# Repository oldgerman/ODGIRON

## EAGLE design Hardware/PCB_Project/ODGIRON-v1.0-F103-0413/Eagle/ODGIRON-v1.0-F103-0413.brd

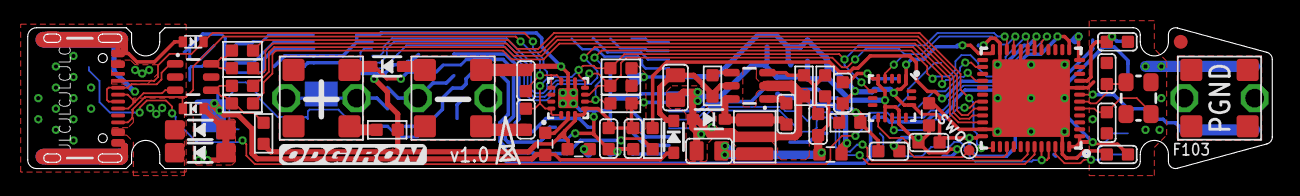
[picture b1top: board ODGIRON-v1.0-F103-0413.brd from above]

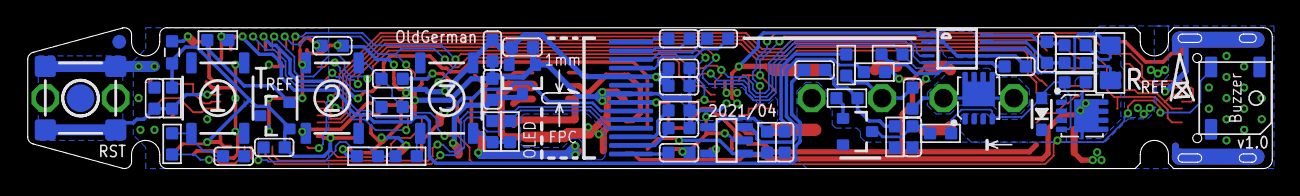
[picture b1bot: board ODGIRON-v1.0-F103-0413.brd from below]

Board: 2 copper layers, 89.8 x 10.2 mm, 123 parts (57 on the bottom side), 66 nets.

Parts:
AMP1: SGM8551XN5G/TR; SOT23-5
BUZ1: BUZZER_5020
C1, C2, C3, C4, C5, C6, C10, C11, C12, C13, C14, C16, C29: 0.1uF/50V; C0603
C7, C23: 4.7uF/10V; C0603
C8, C9: 10pF/50V; C0603
C15, C21, C22, C24, C31, C39: 1uF/16V; C0603
C17, C27: 10nF/50V; C0603
C18, C19: 470pF/50V; C0603
C20, C25, C26, C37: 10uF/10V; C0603
C30: 10uF/25V; C0805
C32: 100pF; C0603
C33: 4.7uF/50V; C0805
C34: 100pF/50V; C0603
CP1: FUSE_CLIPS_01
D1, D7, D9: B5819WS; SOD-323
D2, D5: SMF26A; SOD-123
D3: MMSZ5242BS-7-F; SOD-323
D6, D8: ESD5B5.0ST1; SOD-523
DA1: INA226; MSOP10
FB1, FB2, FB3, FB4, FB5: 1K; F0603
FID1, FID2: FIDUCIAL; FIDUCIAL_1MM
J3: USB-C-16P
L1: 33uH CBC3225T330KR; SMD,3.2X2.5X2.5MM
LCD1: 0.87inch SSD1316; 0.87INCH_128X32_OLED_SSD1306
LOGO1: OSHW-LOGONO_SILK; DUMMY
PAD1, PAD2, PAD3, PAD4, PAD5, PAD6, PAD7, PAD8, PAD9, PAD10, PAD11, PAD12: PADTP16SQ; TP16SQ
Q2, Q3: AON7403; DFN8P-0.65-3X3X0.8MM
Q4: 600mA/40V; SOT23-3
R1, R13: 32.4K; R0603
R2: 124K; R0603
R3, R10, R16, R18, R19, R22, R25, R35: 4.7K; R0603
R4: 1.5K; R0603
R5, R6, R27, R28: 22R; R0603
R7, R12, R23, R41, R45: 1K; R0603
R8, R20, R42: 100K; R0603
R9, R11, R14, R38: 10K; R0603
R17: 560K; R0603
R24: 10mR ±1% ±50ppm/°C; R1206
R36, R37: 10R; R0603
R43: 2.4K ±0.1% ±25ppm/℃; R0603
R44: 750K ±0.1% ±25ppm/℃; R0603
S1, S2, S3, S5: TACTILE_SWITCH_SMD
T1: HAKKO_T12_K-TYPE_WITH_FUSE_CLIPS_X2
TP1: PGND; TESTPOINT_ROUND_2MM
TP5: SWO; PAD.03X.03
U1: FUSB302BMPX; QFN14-2.5X2.5MM
U3: STM32F103CBU6; QFN48_7X7MM_0.5MM
U4: MP2456GJ; SOT23-6
U5: MCP9700AT-E/TT; SOT23-3@1
U6: MCP1700T-3302E/TT; SOT23-3
U8: LIS3DH; LGA-16-3X3
U$3: CREATIVE_COMMONS
VD1: USBLC6-2SC6; SOT23-6
ZO1: 8MHz; 3.2X2.5_KX-7

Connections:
3.9V: C30.1, C32.1, FB1.1, L1.2, R2.1
+3V3: C2.1, C4.1, C5.1, C12.2, C13.2, C14.2, C15.1, C20.2, C23.2, C24.2, C37.2, C39.2, DA1.6, FB2.2, FB3.2, LCD1.5, LCD1.8, R3.1, R4.2, R13.2, R16.1, R18.2, R19.2, R22.2, R23.2, R25.1, R38.1, S3.3, S3.4, U1.3, U1.4, U3.1, U3.24, U3.36, U3.48, U5.1, U6.2, U8.1, U8.14
AMP+: AMP1.3, R42.1
AMP-: AMP1.4, C34.2, R43.1, R44.2
BS: C29.1, U4.1
CC1: C18.1, D8.K, J3.A5, U1.1, U1.14
CC2: C19.1, D6.K, J3.B5, U1.10, U1.11
D+: J3.A6, J3.B6, VD1.3
D-: J3.A7, J3.B7, VD1.1
DCDC_IN: C33.1, D1.C, R20.2, U4.5
EN: R20.1, U4.4
GND: AMP1.2, BUZ1.-, C2.2, C3.2, C4.2, C5.2, C6.2, C7.2, C8.1, C9.1, C10.2, C11.1, C12.1, C13.1, C14.1, C15.2, C16.1, C18.2, C19.2, C20.1, C23.1, C24.1, C25.2, C26.2, C27.2, C30.2, C31.1, C33.2, C37.1, C39.1, D2.A, D5.A, D6.A, D7.A, D8.A, D9.A, DA1.1, DA1.2, DA1.7, FB4.1, FB4.2, J3.GND, J3.GND2, J3.SHLD1, J3.SHLD2, J3.SHLD3, J3.SHLD4, J3.SHLD5, J3.SHLD6, J3.SHLD7, J3.SHLD8, LCD1.7, PAD5.TP, PAD6.TP, PAD7.TP, PAD8.TP, Q4.2, R1.1, R8.2, R12.1, R17.1, R43.2, S1.1, S1.2, S2.1, S2.2, S5.1, S5.2, T1.1A1, T1.1B1, U1.8, U1.9, U1.THERMAL, U3.8, U3.20, U3.23, U3.35, U3.47, U3.P$1, U4.2, U5.3, U6.1, U8.5, U8.10, U8.12, VD1.2, ZO1.2, ZO1.4
LDO_IN: C31.2, FB1.2, U6.3
unnamed: R4.1, R5.1, R27.1, VD1.4
unnamed: R7.2, S3.1, S3.2
unnamed: D3.C, Q2.1, Q2.2, Q2.3, Q3.1, Q3.2, Q3.3
unnamed: C21.1, LCD1.1
unnamed: D3.A, Q2.4, Q3.4, R10.2, R35.1
unnamed: C22.1, LCD1.3
unnamed: C11.2, FB2.1, U3.9
unnamed: C3.1, R9.2, S1.3, S1.4
unnamed: C21.2, LCD1.2
unnamed: C6.1, R14.2, S2.3, S2.4
unnamed: C22.2, LCD1.4
unnamed: C25.1, LCD1.13
unnamed: LCD1.12, R17.2
unnamed: C26.1, LCD1.14
unnamed: Q4.1, R11.1
unnamed: C32.2, R1.2, R2.2, U4.3
unnamed: C16.2, Q4.3, R35.2
unnamed: C17.1, R11.2, R12.2
unnamed: AMP1.5, FB3.1
unnamed: R6.1, R28.1, VD1.6
unnamed: FB5.1, U1.2
unnamed: C1.1, DA1.10, R36.1
unnamed: C1.2, DA1.9, R37.1
unnamed: R41.2, U5.2
NRST: C10.1, R23.1, S5.3, S5.4, U3.7
OSC_IN: C8.2, U3.5, ZO1.3
OSC_OUT: C9.2, U3.6, ZO1.1
OUT: AMP1.1, C34.1, R44.1, R45.2
PA2/ADC2: R41.1, U3.12
PA3/T2C4: C17.2, U3.13
PA7/T1CH1N/T3C2: BUZ1.+, U3.17
PA10/IT_ACCEL_1: U3.31, U8.11
PA11/USB_DM: R6.2, U3.32
PA12/USB_DP: R5.2, U3.33
PA13/SWDIO: R27.2, U3.34
PA14/SWCLK: R28.2, U3.37
PB0/ADC8: R45.1, U3.18
PB1/IT_FUSB302: R16.2, U1.5, U3.19
PB3/IT_ACCEL_2: TP5.P$1, U3.39, U8.9
PB6/SCL1: LCD1.10, R19.1, U3.42
PB7/SDA1: LCD1.11, R18.1, U3.43
PB8&BOOT0_S3: R7.1, R8.1, U3.44, U3.45
PB9/S1: R9.1, U3.46
PB10/SCL2: DA1.5, R3.2, U1.6, U3.21, U8.4
PB11/SDA2: DA1.4, R25.2, U1.7, U3.22, U8.6
PB13/IT_INA226: DA1.3, R38.2, U3.26
PB15/S2: R14.1, U3.28
PGND: CP1.1A, CP1.1B, PAD9.TP, PAD10.TP, PAD11.TP, PAD12.TP, TP1.P$1
RES_3.3V: C7.1, LCD1.9, R22.1
SW: C29.2, D7.C, L1.1, U4.6
T12+: C27.1, D9.C, PAD1.TP, PAD2.TP, PAD3.TP, PAD4.TP, Q3.5, Q3.6, Q3.7, Q3.8, Q3.9, R13.1, R42.2, T1.1A, T1.1B
VBUS-C: D1.A, FB5.2, Q2.5, Q2.6, Q2.7, Q2.8, Q2.9, R10.1, R24.1, R37.2
VUSB_IN: D2.C, D5.C, DA1.8, J3.VBUS1, J3.VBUS2, R24.2, R36.2

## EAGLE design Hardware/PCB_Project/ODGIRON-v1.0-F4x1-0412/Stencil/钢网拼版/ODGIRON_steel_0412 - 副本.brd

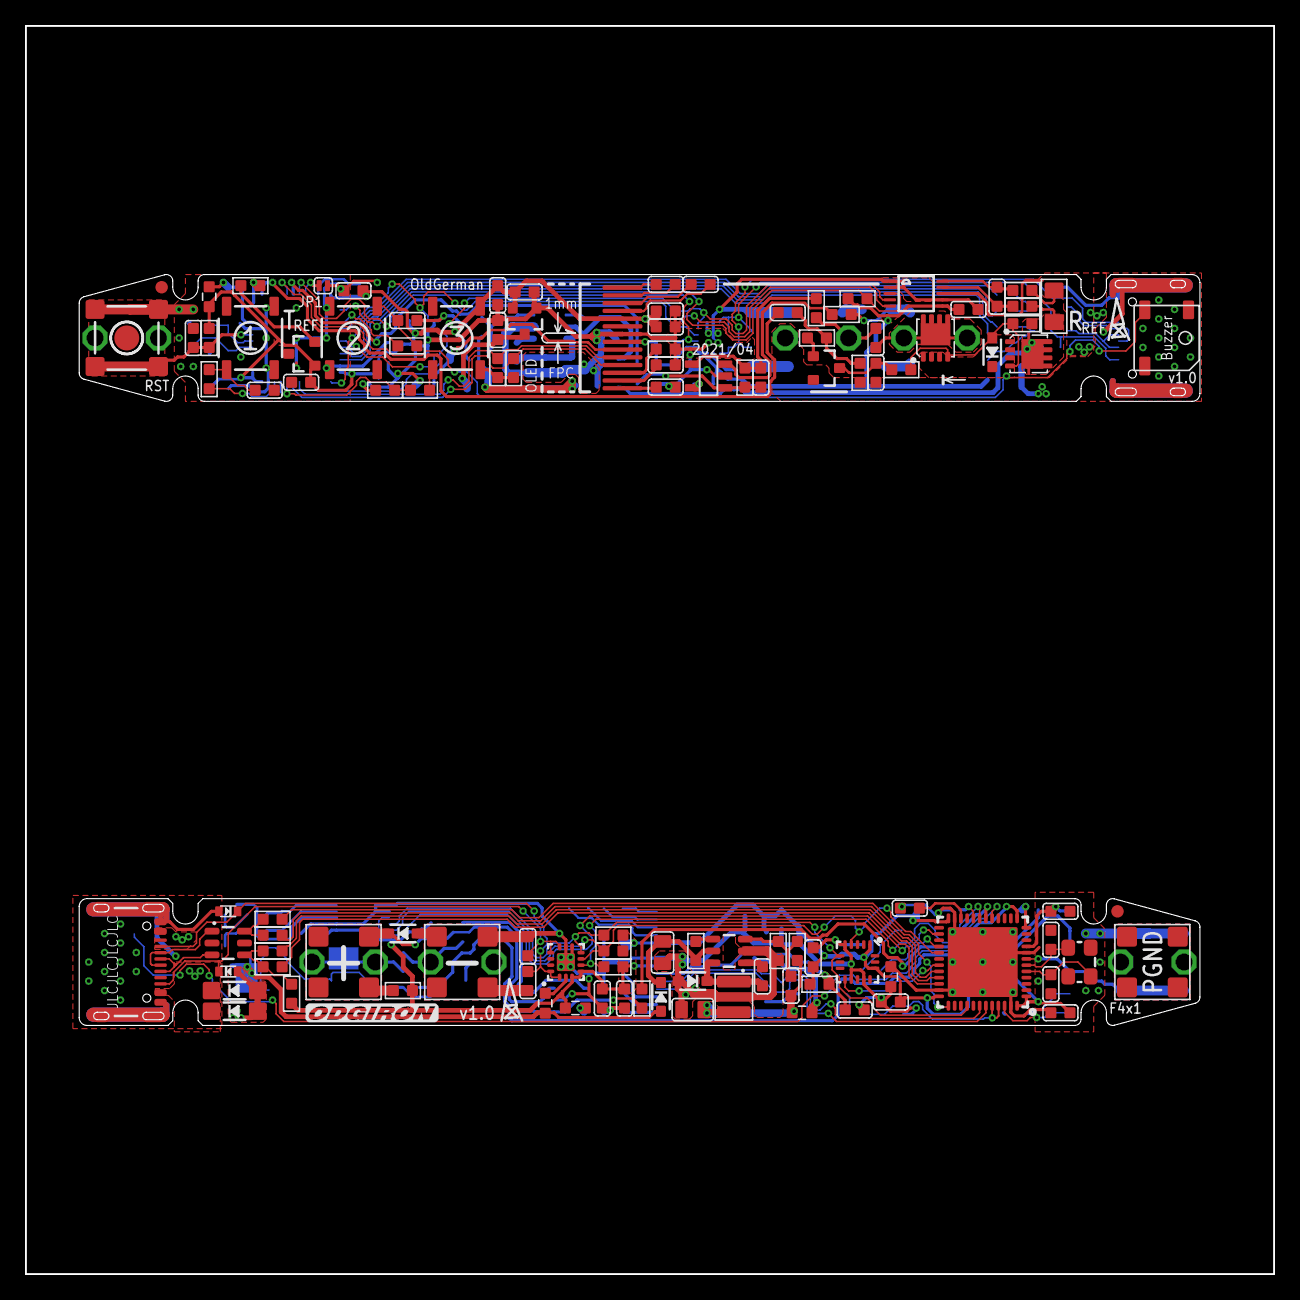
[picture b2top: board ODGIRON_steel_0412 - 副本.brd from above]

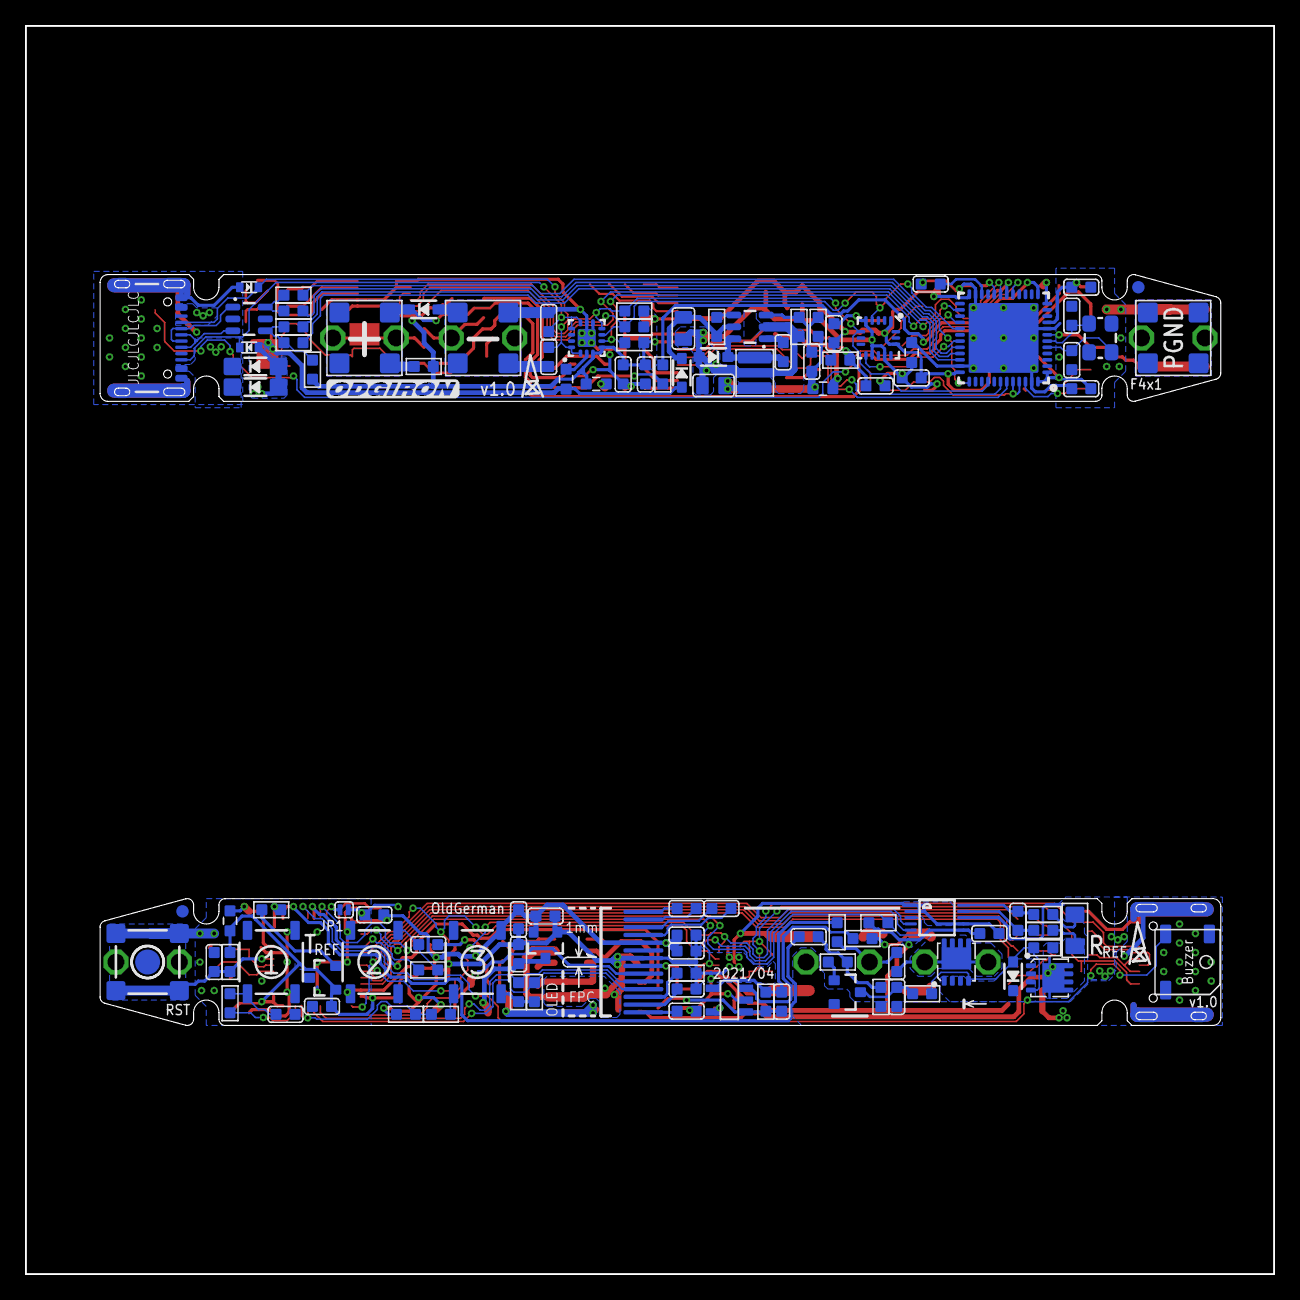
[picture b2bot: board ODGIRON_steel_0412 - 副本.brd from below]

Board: 2 copper layers, 100.0 x 100.0 mm, 245 parts (122 on the bottom side), 134 nets.

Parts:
AMP1, AMP2: SGM8551XN5G/TR; SOT23-5
BUZ1, BUZ2: BUZZER_5020
C1, C2, C3, C4, C5, C6, C10, C11, C12, C13, C14, C16, C29, C38, C40, C41, C42, C43, C52, C53, C54, C58, C59, C61, C68, C70: 0.1uF/50V; C0603
C7, C23, C49, C69: 4.7uF/16V; C0603
C8, C9, C28, C36: 10pF/50V; C0603
C15, C21, C22, C24, C31, C39, C44, C47, C48, C50, C64, C66: 1uF/16V; C0603
C17, C27, C55, C60: 10nF/50V; C0603
C18, C19, C45, C46: 470pF/50V; C0603
C20, C25, C26, C37, C62, C63, C65, C67: 10uF/10V; C0603
C30, C57: 10uF/25V; C0805
C32, C71: 2.2uF/16V; C0603
C33, C51: 4.7uF/50V; C0805
C34, C35, C56, C72: 100pF/50V; C0603
CP1, CP2: FUSE_CLIPS_01
D1, D4, D7, D9, D15, D16: B5819WS; SOD-323
D2, D5, D11, D12: SMF24A; SOD-123
D3, D10: MMSZ5242BS-7-F; SOD-323
D6, D8, D13, D14: ESD5B5.0ST1; SOD-523
DA1, DA2: INA226; MSOP10
FB1, FB2, FB3, FB4, FB5, FB6, FB7, FB8, FB9, FB10: 1K; F0603
FID1, FID2, FID3, FID4: FIDUCIAL; FIDUCIAL_1MM
J1, J3: USB-C-16P
JP1, JP2: SMT-JUMPER_2_NO_SILK
L1, L2: 33uH CBC3225T330KR; SMD,3.2X2.5X2.5MM
LCD1, LCD2: 0.87inch SSD1306; 0.87INCH_128X32_OLED_SSD1306
LOGO1: OSHW-LOGONO_SILK; DUMMY
PAD1, PAD2, PAD3, PAD4, PAD5, PAD6, PAD7, PAD8, PAD9, PAD10, PAD11, PAD12, PAD13, PAD14, PAD15, PAD16, PAD17, PAD18, PAD19, PAD20, PAD21, PAD22, PAD23, PAD24: PADTP16SQ; TP16SQ
Q1, Q2, Q3, Q5: AON7403; DFN8P-0.65-3X3X0.8MM
Q4, Q6: S8050; SOT23-3
R1, R13, R49, R68: 32.4K; R0603
R2, R50: 124K; R0603
R3, R10, R16, R18, R19, R22, R25, R32, R33, R34, R35, R40, R46, R47, R53, R62: 4.7K; R0603
R4, R15: 1.5K; R0603
R5, R6, R27, R28, R30, R31, R51, R52: 22R; R0603
R7, R12, R23, R26, R41, R45, R56, R60, R64, R67: 1K; R0603
R8, R20, R29, R42, R48, R57: 100K; R0603
R9, R11, R14, R21, R38, R63, R65, R66: 10K; R0603
R17, R39: 560K; R0603
R24, R61: 10mR ±1% ±50ppm/℃; R1206
R36, R37, R54, R55: 10R; R0603
R43, R58: 2.37K ±0.1% ±25ppm/℃; R0603
R44, R59: 750K ±0.1% ±25ppm/℃; R0603
S1, S2, S3, S4, S5, S6, S7, S8: TACTILE_SWITCH_SMD
T1, T2: HAKKO_T12_K-TYPE_WITH_FUSE_CLIPS_X2
TP1, TP2: PGND; TESTPOINT_ROUND_2MM
U1, U13: FUSB302BMPX; QFN14-2.5X2.5MM
U3, U12: STM32F4x1CxU6; QFN48_7X7MM_0.5MM
U4, U14: MP2456GJ; SOT23-6
U5, U15: MCP9700AT-E/TT,or LM50CIM3X; SOT23-3@1
U6, U16: MCP1700T-3302E/TT; SOT23-3
U8, U17: LIS3DH; LGA-16-3X3
VD1, VD2: USBLC6-2SC6; SOT23-6
ZO1, ZO2: 8MHz; 3.2X2.5_KX-7

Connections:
3.9V: C30.1, C35.1, FB1.1, L1.2, R2.1
3.9V1: C57.1, C72.1, FB7.1, L2.2, R50.1
+3V1: C40.2, C41.2, C42.2, C43.1, C44.1, C49.2, C50.2, C53.1, C54.1, C65.2, C66.2, C67.2, DA2.6, FB6.2, FB8.2, LCD2.5, LCD2.8, R15.2, R32.1, R33.1, R34.1, R40.2, R46.2, R47.2, R65.1, R67.2, R68.2, S4.3, S4.4, U12.1, U12.24, U12.36, U12.48, U13.3, U13.4, U15.1, U16.2, U17.1, U17.14
+3V3: C2.1, C4.1, C5.1, C12.2, C13.2, C14.2, C15.1, C20.2, C23.2, C24.2, C37.2, C39.2, DA1.6, FB2.2, FB3.2, LCD1.5, LCD1.8, R3.1, R4.2, R13.2, R16.1, R18.2, R19.2, R22.2, R23.2, R25.1, R38.1, S3.3, S3.4, U1.3, U1.4, U3.1, U3.24, U3.36, U3.48, U5.1, U6.2, U8.1, U8.14
AMP+: AMP1.3, R42.1
AMP+1: AMP2.3, R57.1
AMP-: AMP1.4, C34.2, R43.1, R44.2
AMP-1: AMP2.4, C56.2, R58.1, R59.2
BS: C29.1, U4.1
BS1: C61.1, U14.1
CC1: C18.1, D8.K, J3.A5, U1.1, U1.14
CC2: C19.1, D6.K, J3.B5, U1.10, U1.11
CC3: C46.1, D13.K, J1.B5, U13.10, U13.11
CC4: C45.1, D14.K, J1.A5, U13.1, U13.14
D+: J3.A6, J3.B6, VD1.3
D+1: J1.A6, J1.B6, VD2.3
D-: J3.A7, J3.B7, VD1.1
D-1: J1.A7, J1.B7, VD2.1
DCDC_IN: C33.1, D1.C, R20.2, U4.5
DCDC_IN1: C51.1, D15.C, R48.2, U14.5
EN: R20.1, U4.4
EN1: R48.1, U14.4
GND: AMP1.2, BUZ1.-, C2.2, C3.2, C4.2, C5.2, C6.2, C7.2, C8.1, C9.1, C10.2, C11.1, C12.1, C13.1, C14.1, C15.2, C16.1, C18.2, C19.2, C20.1, C23.1, C24.1, C25.2, C26.2, C27.2, C30.2, C31.1, C32.2, C33.2, C37.1, C39.1, D2.A, D5.A, D6.A, D7.A, D8.A, D9.A, DA1.1, DA1.2, DA1.7, FB4.1, FB4.2, J3.GND, J3.GND2, J3.SHLD1, J3.SHLD2, J3.SHLD3, J3.SHLD4, J3.SHLD5, J3.SHLD6, J3.SHLD7, J3.SHLD8, JP1.1, LCD1.7, PAD5.TP, PAD6.TP, PAD7.TP, PAD8.TP, Q4.2, R1.1, R8.2, R12.1, R17.1, R43.2, S1.1, S1.2, S2.1, S2.2, S5.1, S5.2, T1.1A1, T1.1B1, U1.8, U1.9, U1.THERMAL, U3.8, U3.23, U3.35, U3.47, U3.P$1, U4.2, U5.3, U6.1, U8.5, U8.10, U8.12, VD1.2, ZO1.2, ZO1.4
GND1: AMP2.2, BUZ2.-, C28.1, C36.1, C38.1, C40.1, C41.1, C42.1, C43.2, C44.2, C45.2, C46.2, C49.1, C50.1, C51.2, C53.2, C54.2, C55.2, C57.2, C58.2, C59.1, C62.2, C63.2, C64.1, C65.1, C66.1, C67.1, C68.2, C69.2, C70.2, C71.2, D4.A, D11.A, D12.A, D13.A, D14.A, D16.A, DA2.1, DA2.2, DA2.7, FB9.1, FB9.2, J1.GND, J1.GND2, J1.SHLD1, J1.SHLD2, J1.SHLD3, J1.SHLD4, J1.SHLD5, J1.SHLD6, J1.SHLD7, J1.SHLD8, JP2.1, LCD2.7, PAD17.TP, PAD18.TP, PAD19.TP, PAD20.TP, Q6.2, R29.2, R39.1, R49.1, R58.2, R64.1, S6.1, S6.2, S7.1, S7.2, S8.1, S8.2, T2.1A1, T2.1B1, U12.8, U12.23, U12.35, U12.47, U12.P$1, U13.8, U13.9, U13.THERMAL, U14.2, U15.3, U16.1, U17.5, U17.10, U17.12, VD2.2, ZO2.2, ZO2.4
LDO_IN: C31.2, FB1.2, U6.3
LDO_IN1: C64.2, FB7.2, U16.3
unnamed: R7.2, S3.1, S3.2
unnamed: C11.2, FB2.1, U3.9
unnamed: C21.2, LCD1.2
unnamed: C22.2, LCD1.4
unnamed: C25.1, LCD1.13
unnamed: LCD1.12, R17.2
unnamed: C26.1, LCD1.14
unnamed: C35.2, R1.2, R2.2, U4.3
unnamed: C22.1, LCD1.3
unnamed: C21.1, LCD1.1
unnamed: C3.1, R9.2, S1.3, S1.4
unnamed: D3.C, Q2.1, Q2.2, Q2.3, Q3.1, Q3.2, Q3.3
unnamed: D3.A, Q2.4, Q3.4, R10.2, R35.1
unnamed: C16.2, Q4.3, R35.2
unnamed: Q4.1, R11.1
unnamed: C17.1, R11.2, R12.2
unnamed: C6.1, R14.2, S2.3, S2.4
unnamed: R4.1, R5.1, R27.1, VD1.4
unnamed: C1.1, DA1.10, R36.1
unnamed: C1.2, DA1.9, R37.1
unnamed: R41.2, U5.2
unnamed: R6.1, R28.1, VD1.6
unnamed: FB5.1, U1.2
unnamed: AMP1.5, FB3.1
unnamed: JP1.2, U3.20
unnamed: R26.2, S4.1, S4.2
unnamed: C38.2, FB6.1, U12.9
unnamed: C47.2, LCD2.2
unnamed: C48.2, LCD2.4
unnamed: C62.1, LCD2.13
unnamed: LCD2.12, R39.2
unnamed: C63.1, LCD2.14
unnamed: C72.2, R49.2, R50.2, U14.3
unnamed: C52.1, DA2.10, R54.1
unnamed: C52.2, DA2.9, R55.1
unnamed: C48.1, LCD2.3
unnamed: C47.1, LCD2.1
unnamed: C58.1, R21.2, S6.3, S6.4
unnamed: D10.C, Q1.1, Q1.2, Q1.3, Q5.1, Q5.2, Q5.3
unnamed: D10.A, Q1.4, Q5.4, R53.1, R62.2
unnamed: C59.2, Q6.3, R53.2
unnamed: Q6.1, R63.1
unnamed: C60.1, R63.2, R64.2
unnamed: R56.2, U15.2
unnamed: C68.1, R66.2, S7.3, S7.4
unnamed: R15.1, R30.1, R51.1, VD2.4
unnamed: R31.1, R52.1, VD2.6
unnamed: FB10.1, U13.2
unnamed: AMP2.5, FB8.1
unnamed: JP2.2, U12.20
NRST: C10.1, R23.1, S5.3, S5.4, U3.7
NRST1: C70.1, R67.1, S8.3, S8.4, U12.7
OSC_IN: C8.2, U3.5, ZO1.3
OSC_IN1: C36.2, U12.5, ZO2.3
OSC_OUT: C9.2, U3.6, ZO1.1
OSC_OUT1: C28.2, U12.6, ZO2.1
OUT: AMP1.1, C34.1, R44.1, R45.2
OUT1: AMP2.1, C56.1, R59.1, R60.2
PA2/ADC1: R56.1, U12.12
PA2/ADC2: R41.1, U3.12
PA3/T2C1: C60.2, U12.13
PA3/T2C4: C17.2, U3.13
PA7/T1CH1N/T3C1: BUZ2.+, U12.17
PA7/T1CH1N/T3C2: BUZ1.+, U3.17
PA8/SCL1: DA2.5, R33.2, U12.29, U13.6, U17.4
PA8/SCL3: DA1.5, R3.2, U1.6, U3.29, U8.4
PA10/IT_ACCEL_1: U12.31, U17.9
PA10/IT_ACCEL_2: U3.31, U8.9
PA11/USB_DM: R6.2, U3.32
PA11/USB_DM1: R31.2, U12.32
PA12/USB_DP: R5.2, U3.33
PA12/USB_DP1: R30.2, U12.33
PA13/SWDIO: R27.2, U3.34
PA13/SWDIO1: R51.2, U12.34
PA14/SWCLK: R28.2, U3.37
PA14/SWCLK1: R52.2, U12.37
PB0/ADC1: R60.1, U12.18
PB0/ADC8: R45.1, U3.18
PB1/IT_FUSB1: R34.2, U12.19, U13.5
PB1/IT_FUSB302: R16.2, U1.5, U3.19
PB4/SDA1: DA2.4, R32.2, U12.40, U13.7, U17.6
PB4/SDA3: DA1.4, R25.2, U1.7, U3.40, U8.6
PB6/SCL1: LCD1.10, R19.1, U3.42
PB6/SCL2: LCD2.10, R46.1, U12.42
PB7/SDA1: LCD1.11, R18.1, U3.43
PB7/SDA2: LCD2.11, R40.1, U12.43
PB8&BOOT0_S1: R26.1, R29.1, U12.44, U12.45
PB8&BOOT0_S3: R7.1, R8.1, U3.44, U3.45
PB9/S1: R9.1, U3.46
PB9/S2: R21.1, U12.46
PB13/IT_INA1: DA2.3, R65.2, U12.26
PB13/IT_INA226: DA1.3, R38.2, U3.26
PB15/S1: R66.1, U12.28
PB15/S2: R14.1, U3.28
PGND1: CP1.1A, CP1.1B, PAD9.TP, PAD10.TP, PAD11.TP, PAD12.TP, TP1.P$1
PGND2: CP2.1A, CP2.1B, PAD21.TP, PAD22.TP, PAD23.TP, PAD24.TP, TP2.P$1
RES_3.3V: C7.1, LCD1.9, R22.1
RES_3.3V1: C69.1, LCD2.9, R47.1
SW: C29.2, D7.C, L1.1, U4.6
SW1: C61.2, D4.C, L2.1, U14.6
T12+: C27.1, D9.C, PAD1.TP, PAD2.TP, PAD3.TP, PAD4.TP, Q3.5, Q3.6, Q3.7, Q3.8, Q3.9, R13.1, R42.2, T1.1A, T1.1B
T12+1: C55.1, D16.C, PAD13.TP, PAD14.TP, PAD15.TP, PAD16.TP, Q1.5, Q1.6, Q1.7, Q1.8, Q1.9, R57.2, R68.1, T2.1A, T2.1B
VBUS-C: D1.A, FB5.2, Q2.5, Q2.6, Q2.7, Q2.8, Q2.9, R10.1, R24.1, R37.2
VBUS-C1: D15.A, FB10.2, Q5.5, Q5.6, Q5.7, Q5.8, Q5.9, R55.2, R61.1, R62.1
VCAP1: C32.1, U3.22
VCAP2: C71.1, U12.22
VUSB_IN: D2.C, D5.C, DA1.8, J3.VBUS1, J3.VBUS2, R24.2, R36.2
VUSB_IN1: D11.C, D12.C, DA2.8, J1.VBUS1, J1.VBUS2, R54.2, R61.2

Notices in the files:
parts and their libraries:
SparkFun-Aesthetics: Licensing: Creative Commons ShareAlike 4.0 International - https://creativecommons.org/licenses/by-sa/4.0
SparkFun-Aesthetics: Released under the Creative Commons Attribution Share-Alike 4.0 License
SparkFun-Aesthetics: https://creativecommons.org/licenses/by-sa/4.0
